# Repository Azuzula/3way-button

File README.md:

# 3way-button breakout board for MCPL3-AC-V

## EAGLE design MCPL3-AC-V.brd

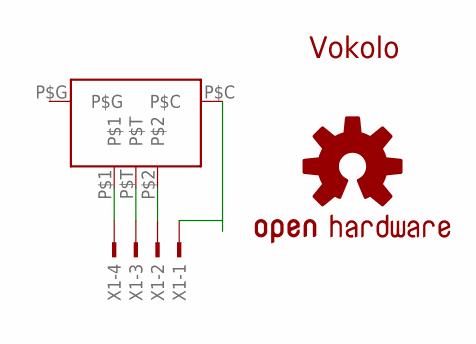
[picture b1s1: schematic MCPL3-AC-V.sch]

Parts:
LOGO1: OSHW-LOGOMINI; OSHW-LOGO-MINI
U$1: MCPL3-AC-VWIDE; MCPL3-AC-V-EDITED
U$2: LOGO_VOKOLO12MM; LOGO_VOKOLO_9,8MM
X1: TSW-104-07-G-S; TSW-104-XX-G-S

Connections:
unnamed: U$1.P$1, X1.4
unnamed: U$1.P$T, X1.3
unnamed: U$1.P$2, X1.2
unnamed: U$1.P$C, X1.1

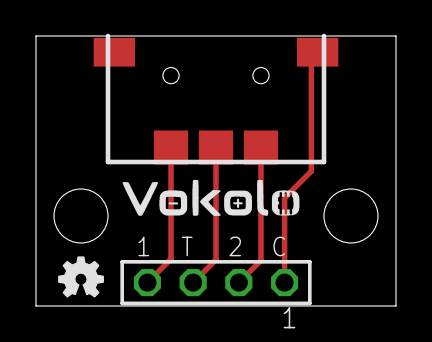
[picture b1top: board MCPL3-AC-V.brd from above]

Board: 2 copper layers, 20.0 x 15.0 mm, 4 parts (0 on the bottom side), 4 nets.

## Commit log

2023-10-09 Add files via upload
    New logo update
2023-10-09 Add files via upload
    Gerber files.

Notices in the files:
parts and their libraries:
SparkFun-Aesthetics: Licensing: Creative Commons ShareAlike 4.0 International - https://creativecommons.org/licenses/by-sa/4.0
